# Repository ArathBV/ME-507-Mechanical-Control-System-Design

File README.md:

# ME-507-Mechanical-Control-System-Design
This is a repository containing assignments and coursework from ME 507 Mechanical Control System Design at California Polytechnic State University.

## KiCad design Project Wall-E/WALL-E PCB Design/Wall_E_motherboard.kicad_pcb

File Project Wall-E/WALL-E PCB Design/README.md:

# PCB Design Layout for WALL-E
## Authors: Devon Bolt, Arath Villanueva
- 4 Layer PCB
  - Middle Layer 1, Ground Plane and a 5V bus
  - Middle Layer 2, 3.3V Plane and a 5V bus
    
### Schematic
- 
  - **Full Schematic**

  - **Power Distribution**
### PCB Layout
- 
  - **Top and Bottom Layer**
- 
  - **Middle Layer 1: Ground Plane**
- 
  - **Middle Layer 2: 3.3V Plane**
### PCB CAD Model
-

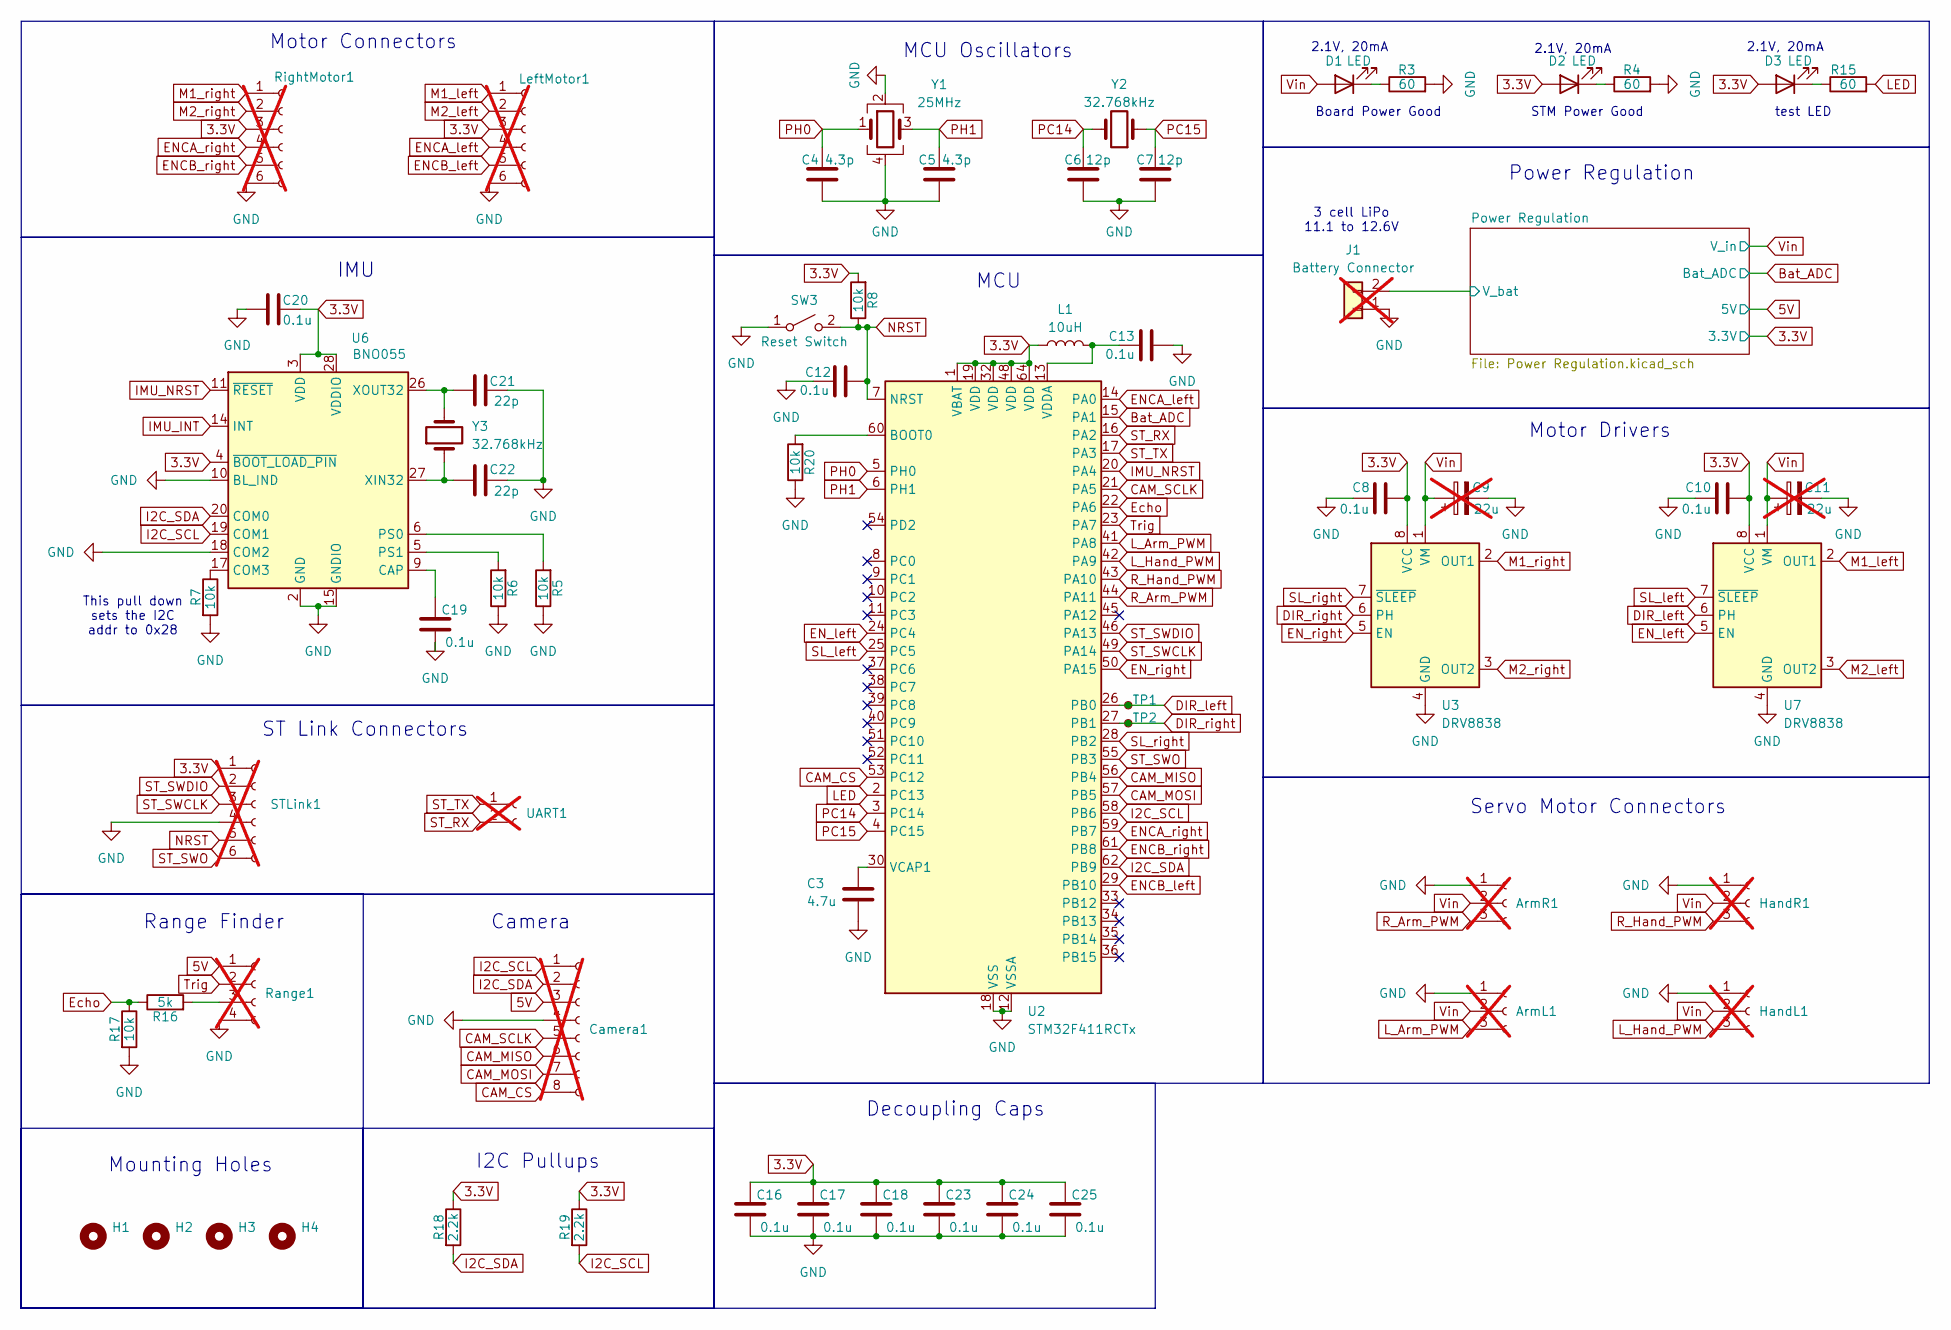
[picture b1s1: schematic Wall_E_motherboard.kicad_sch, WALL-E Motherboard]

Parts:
ArmL1: Conn_01x03_Socket; PinHeader_1x03_P2.54mm_Vertical; not fitted
ArmR1: Conn_01x03_Socket; PinHeader_1x03_P2.54mm_Vertical; not fitted
C3: 4.7u; C_0603_1608Metric
C4, C5: 4.3p; C_0603_1608Metric
C6, C7: 12p; C_0603_1608Metric
C8, C10, C12, C13, C16, C17, C18, C19, C20, C23, C24, C25: 0.1u; C_0603_1608Metric
C9, C11: 22u; CP_Radial_D5.0mm_P2.00mm; not fitted
C21, C22: 22p; C_0603_1608Metric
Camera1: Conn_01x08_Socket; PinHeader_1x08_P2.54mm_Vertical; not fitted
D1, D2, D3: LED; LED_0603_1608Metric
H1, H2, H3, H4: MountingHole; MountingHole_3.2mm_M3
HandL1: Conn_01x03_Socket; PinHeader_1x03_P2.54mm_Vertical; not fitted
HandR1: Conn_01x03_Socket; PinHeader_1x03_P2.54mm_Vertical; not fitted
J1: Conn_01x02; AMASS_XT30PW-M_1x02_P2.50mm_Horizontal; not fitted
L1: 10uH; L_1008_2520Metric
LeftMotor1: Conn_01x06_Socket; PinHeader_1x06_P2.54mm_Vertical; not fitted
R3, R4, R15: 60; R_0603_1608Metric
R5, R6, R7, R8, R17, R20: 10k; R_0603_1608Metric
R16: 5k; R_0603_1608Metric
R18, R19: 2.2k; R_0603_1608Metric
Range1: Conn_01x04_Socket; PinHeader_1x04_P2.54mm_Vertical; not fitted
RightMotor1: Conn_01x06_Socket; PinHeader_1x06_P2.54mm_Vertical; not fitted
STLink1: Conn_01x06_Socket; PinHeader_1x06_P2.54mm_Horizontal; not fitted
SW3: SW_SPST; SW_SPST_PTS645
TP1, TP2: TestPoint_Small; TestPoint_Pad_D1.0mm
U2: STM32F411RCTx; LQFP-64_10x10mm_P0.5mm
U3, U7: DRV8838; WSON-8-1EP_2x2mm_P0.5mm_EP0.9x1.6mm
U6: BNO055; LGA-28_5.2x3.8mm_P0.5mm
UART1: Conn_01x02_Socket; PinHeader_1x02_P2.54mm_Horizontal; not fitted
Y1: 25MHz; Crystal_SMD_3225-4Pin_3.2x2.5mm
Y2, Y3: 32.768kHz; Crystal_SMD_3215-2Pin_3.2x1.5mm

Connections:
3.3V: C8.1, C10.1, C16.1, C17.1, C18.1, C20.2, C23.1, C24.1, C25.1, D2.2 (A), D3.2 (A), L1.1, LeftMotor1.3, R8.2, R18.1, R19.1, RightMotor1.3, STLink1.1, U2.1 (VBAT), U2.19 (VDD), U2.32 (VDD), U2.48 (VDD), U2.64 (VDD), U3.8 (VCC), U6.3 (VDD), U6.4 (~BOOT_LOAD_PIN), U6.28 (VDDIO), U7.8 (VCC); also elsewhere on the board
5V: Camera1.3, Range1.1; also elsewhere on the board
/Power Regulation/V_bat: J1.2; also elsewhere on the board
Bat_ADC: U2.15 (PA1); also elsewhere on the board
CAM_CS: Camera1.8, U2.53 (PC12)
CAM_MISO: Camera1.6, U2.56 (PB4)
CAM_MOSI: Camera1.7, U2.57 (PB5)
CAM_SCLK: Camera1.5, U2.21 (PA5)
DIR_left: TP1.1, U2.26 (PB0), U7.6 (PH)
DIR_right: TP2.1, U2.27 (PB1), U3.6 (PH)
ENCA_left: LeftMotor1.4, U2.14 (PA0)
ENCA_right: RightMotor1.4, U2.59 (PB7)
ENCB_left: LeftMotor1.5, U2.29 (PB10)
ENCB_right: RightMotor1.5, U2.61 (PB8)
EN_left: U2.24 (PC4), U7.5 (EN)
EN_right: U2.50 (PA15), U3.5 (EN)
Echo: R16.1, R17.1, U2.22 (PA6)
GND: ArmL1.1, ArmR1.1, C3.2, C4.2, C5.2, C6.2, C7.2, C8.2, C9.2, C10.2, C11.2, C12.2, C13.2, C16.2, C17.2, C18.2, C19.2, C20.1, C21.2, C22.2, C23.2, C24.2, C25.2, Camera1.4, HandL1.1, HandR1.1, J1.1, LeftMotor1.6, R3.2, R4.2, R5.1, R6.1, R7.2, R17.2, R20.1, Range1.4, RightMotor1.6, STLink1.4, SW3.1 (A), U2.12 (VSSA), U2.18 (VSS), U2.31 (VSS), U2.47 (VSS), U2.63 (VSS), U3.4 (GND), U3.9 (GND), U6.2 (GND), U6.10 (BL_IND), U6.15 (GNDIO), U6.16 (GNDIO), U6.18 (COM2), U6.25 (GNDIO), U7.4 (GND), U7.9 (GND), Y1.2, Y1.4; also elsewhere on the board
I2C_SCL: Camera1.1, R19.2, U2.58 (PB6), U6.19 (COM1)
I2C_SDA: Camera1.2, R18.2, U2.62 (PB9), U6.20 (COM0)
IMU_INT: U6.14 (INT)
IMU_NRST: U2.20 (PA4), U6.11 (~RESET)
LED: R15.2, U2.2 (PC13)
L_Arm_PWM: ArmL1.3, U2.41 (PA8)
L_Hand_PWM: HandL1.3, U2.42 (PA9)
M1_left: LeftMotor1.1, U7.2 (OUT1)
M1_right: RightMotor1.1, U3.2 (OUT1)
M2_left: LeftMotor1.2, U7.3 (OUT2)
M2_right: RightMotor1.2, U3.3 (OUT2)
NRST: C12.1, R8.1, STLink1.5, SW3.2 (B), U2.7 (NRST)
unnamed: D1.1 (K), R3.1
unnamed: D2.1 (K), R4.1
unnamed: D3.1 (K), R15.1
unnamed: R16.2, Range1.3
unnamed: R20.2, U2.60 (BOOT0)
unnamed: C3.1, U2.30 (VCAP1)
unnamed: C13.1, L1.2, U2.13 (VDDA)
unnamed: C19.1, U6.9 (CAP)
unnamed: R7.1, U6.17 (COM3)
unnamed: R5.2, U6.6 (PS0)
unnamed: R6.2, U6.5 (PS1)
unnamed: C22.1, U6.27 (XIN32), Y3.1
unnamed: C21.1, U6.26 (XOUT32), Y3.2
PC14: C6.1, U2.3 (PC14), Y2.2
PC15: C7.1, U2.4 (PC15), Y2.1
PH0: C4.1, U2.5 (PH0), Y1.1
PH1: C5.1, U2.6 (PH1), Y1.3
R_Arm_PWM: ArmR1.3, U2.44 (PA11)
R_Hand_PWM: HandR1.3, U2.43 (PA10)
SL_left: U2.25 (PC5), U7.7 (~SLEEP)
SL_right: U2.28 (PB2), U3.7 (~SLEEP)
ST_RX: U2.16 (PA2), UART1.2
ST_SWCLK: STLink1.3, U2.49 (PA14)
ST_SWDIO: STLink1.2, U2.46 (PA13)
ST_SWO: STLink1.6, U2.55 (PB3)
ST_TX: U2.17 (PA3), UART1.1
Trig: Range1.2, U2.23 (PA7)
Vin: ArmL1.2, ArmR1.2, C9.1, C11.1, D1.2 (A), HandL1.2, HandR1.2, U3.1 (VM), U7.1 (VM); also elsewhere on the board

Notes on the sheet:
Decoupling Caps
STM Power Good
Board Power Good
Range Finder
Power Regulation
Mounting Holes
Camera
MCU Oscillators
Motor Connectors
Servo Motor Connectors
ST Link Connectors
2.1V, 20mA
IMU
Motor Drivers
I2C Pullups
3 cell LiPo 11.1 to 12.6V
test LED
This pull down sets the I2C addr to 0x28
MCU

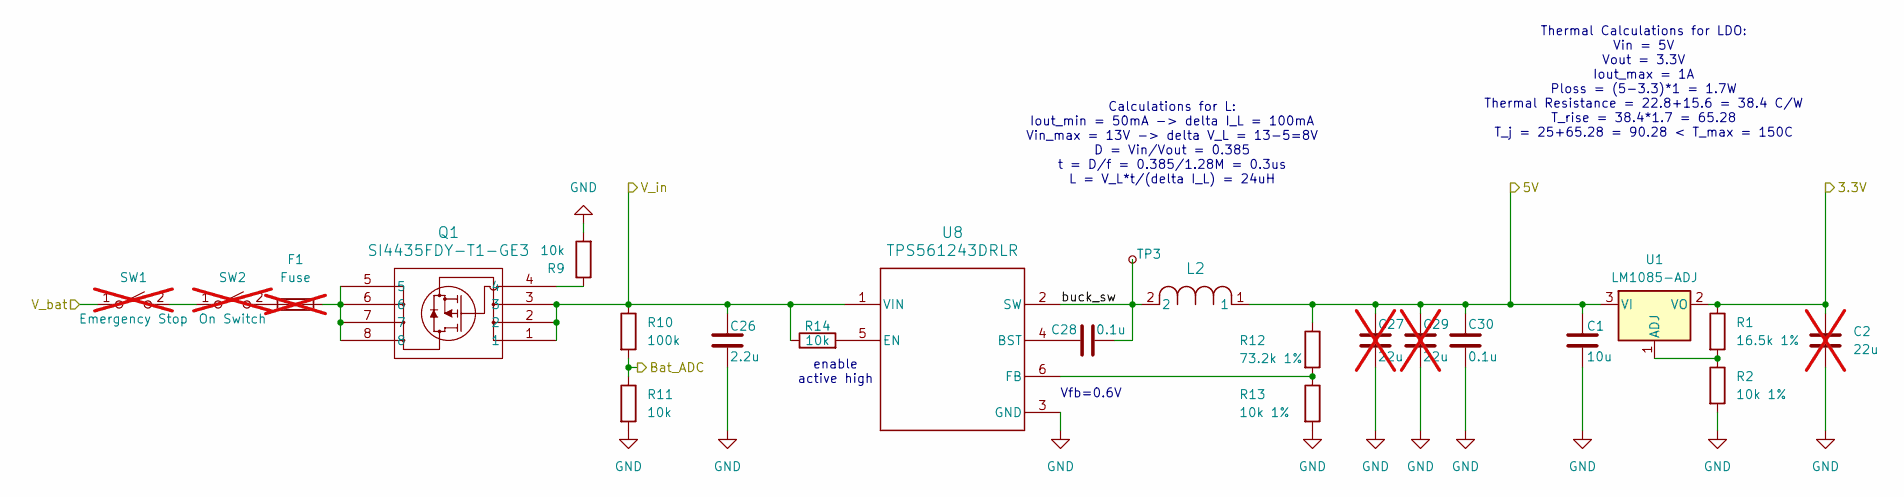
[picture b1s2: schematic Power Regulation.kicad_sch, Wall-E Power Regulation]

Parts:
C1: 10u; C_0603_1608Metric
C2, C27, C29: 22u; CP_Radial_D5.0mm_P2.00mm; not fitted
C26: 2.2u; C_0603_1608Metric
C28, C30: 0.1u; C_0603_1608Metric
F1: Fuse; Fuseholder_Blade_Mini_Keystone_3568; not fitted
L2: IFDC5050HZER270M; IND_IFDC5050HZER_VIS
Q1: SI4435FDY-T1-GE3; SO-8_VIS
R1: 16.5k 1%; R_0603_1608Metric
R2, R13: 10k 1%; R_0603_1608Metric
R9, R11, R14: 10k; R_0603_1608Metric
R10: 100k; R_0603_1608Metric
R12: 73.2k 1%; R_0603_1608Metric
SW1, SW2: SW_SPST; AMASS_XT30PW-F_1x02_P2.50mm_Horizontal; not fitted
TP3: TestPoint_Small; TestPoint_Pad_D1.0mm
U1: LM1085-ADJ; TO-263-3_TabPin2
U8: TPS561243DRLR; DRL0006A-MFG

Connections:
3.3V: C2.1, R1.1, U1.2 (VO); also elsewhere on the board
5V: C1.1, C27.1, C29.1, C30.1, L2.1, R12.1, U1.3 (VI); also elsewhere on the board
/Power Regulation/V_bat: SW1.1 (A); also elsewhere on the board
/Power Regulation/buck_sw: C28.2, L2.2, TP3.1, U8.2 (SW)
Bat_ADC: R10.2, R11.1; also elsewhere on the board
GND: C1.2, C2.2, C26.2, C27.2, C29.2, C30.2, R2.2, R9.2, R11.2, R13.2, U8.3 (GND); also elsewhere on the board
unnamed: F1.2, Q1.5, Q1.6, Q1.7, Q1.8
unnamed: Q1.4, R9.1
unnamed: SW1.2 (B), SW2.1 (A)
unnamed: F1.1, SW2.2 (B)
unnamed: R1.2, R2.1, U1.1 (ADJ)
unnamed: C28.1, U8.4 (BST)
unnamed: R14.2, U8.5 (EN)
unnamed: R12.2, R13.1, U8.6 (FB)
Vin: C26.1, Q1.1, Q1.2, Q1.3, R10.1, R14.1, U8.1 (VIN); also elsewhere on the board

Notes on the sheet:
Vfb=0.6V
Calculations for L: Iout_min = 50mA -> delta I_L = 100mA Vin_max = 13V -> delta V_L = 13-5=8V D = Vin/Vout = 0.385 t = D/f = 0.385/1.28M = 0.3us L = V_L*t/(delta I_L) = 24uH
enable active high
Thermal Calculations for LDO: Vin = 5V Vout = 3.3V Iout_max = 1A Ploss = (5-3.3)*1 = 1.7W Thermal Resistance = 22.8+15.6 = 38.4 C/W T_rise = 38.4*1.7 = 65.28 T_j = 25+65.28 = 90.28 < T_max = 150C

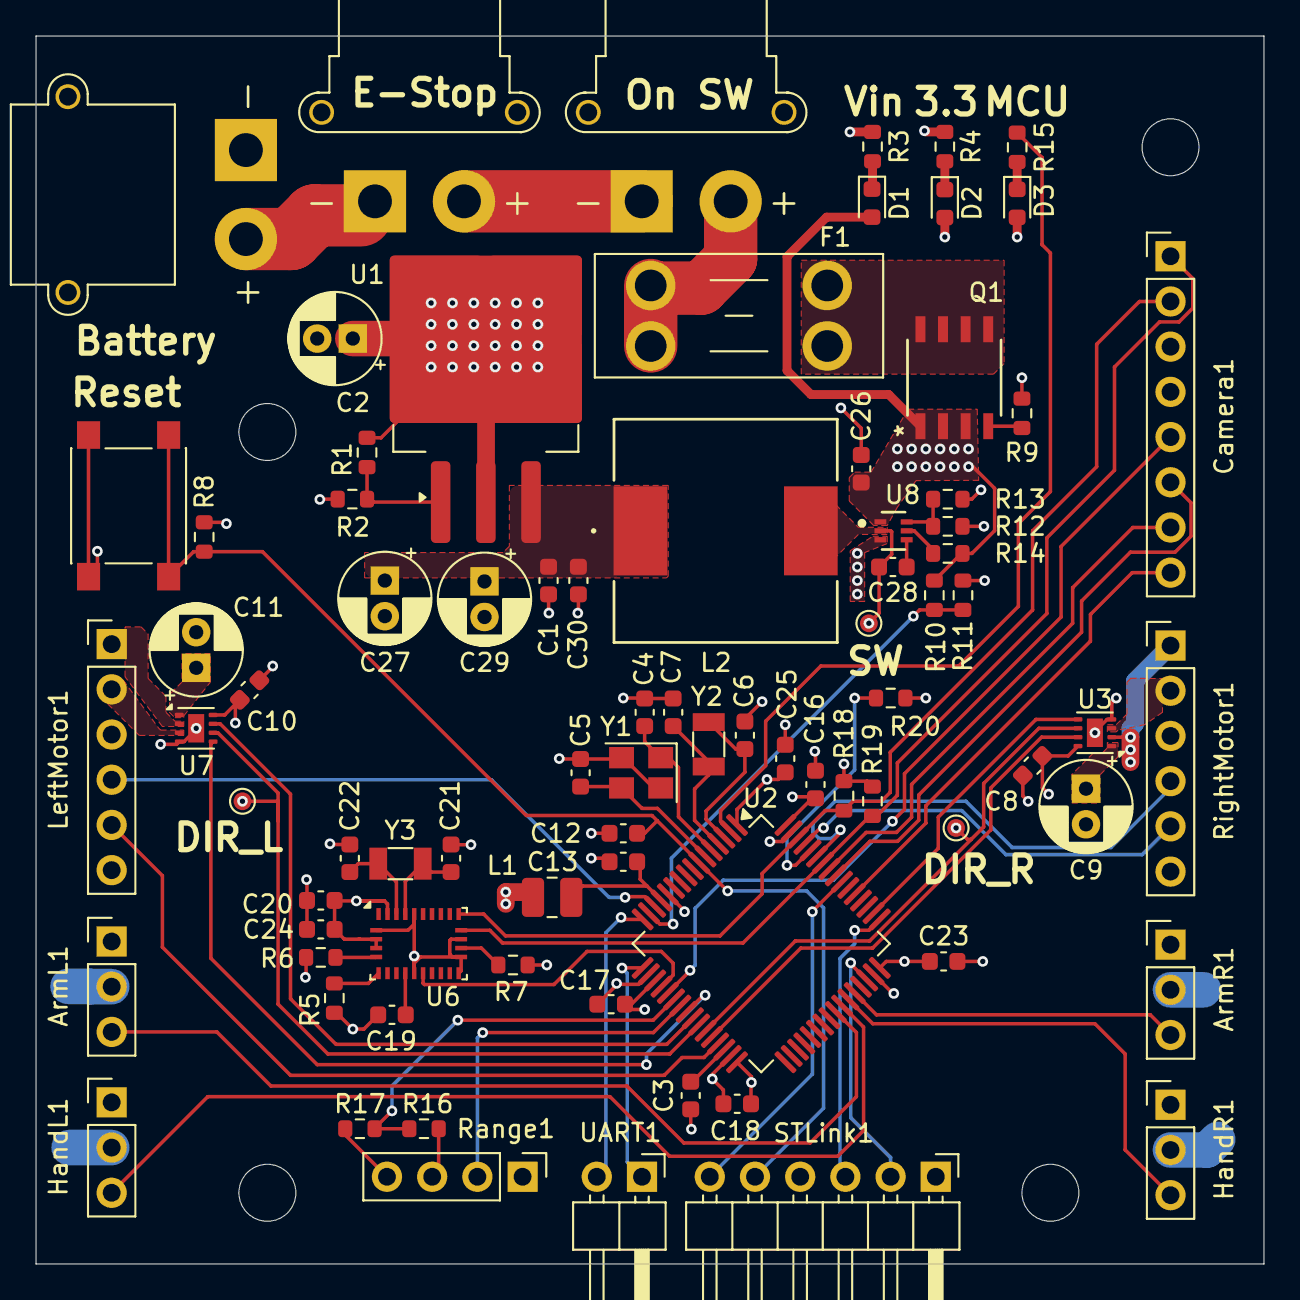
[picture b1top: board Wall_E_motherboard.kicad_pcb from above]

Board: 4 copper layers, 69.0 x 69.0 mm, 85 parts (0 on the bottom side), 66 nets.

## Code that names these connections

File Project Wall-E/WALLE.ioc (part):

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Mcu.Name=STM32F411R(C-E)Tx
Mcu.Package=LQFP64
Mcu.UserName=STM32F411RETx
PA0-WKUP.GPIOParameters=GPIO_Label
PA0-WKUP.GPIO_Label=ENCA_Left
PA0-WKUP.Signal=S_TIM2_CH1_ETR
PA1.GPIOParameters=GPIO_Label
PA1.GPIO_Label=Bat_ADC
PA1.Signal=ADCx_IN1
PA10.GPIOParameters=GPIO_Label
PA10.GPIO_Label=R_HandPWM
PA10.Signal=S_TIM1_CH3
PA11.GPIOParameters=GPIO_Label
PA11.GPIO_Label=R_Arm_PWM
PA11.Signal=S_TIM1_CH4
PA13.Mode=Trace_Asynchronous_SW
PA13.Signal=SYS_JTMS-SWDIO
PA14.Mode=Trace_Asynchronous_SW
PA14.Signal=SYS_JTCK-SWCLK
PA15.GPIOParameters=GPIO_Label
PA15.GPIO_Label=EN_Right
PA15.Signal=GPIO_Output
PA2.Mode=Asynchronous
PA2.Signal=USART2_TX
PA3.Mode=Asynchronous
PA3.Signal=USART2_RX
PA4.GPIOParameters=GPIO_Label
PA4.GPIO_Label=IMU_NRST
PA4.Signal=GPIO_Output
PA5.GPIOParameters=GPIO_Label
PA5.GPIO_Label=CAM_SCLK
PA5.Mode=Full_Duplex_Master
PA5.Signal=SPI1_SCK
PA6.GPIOParameters=GPIO_Label
PA6.GPIO_Label=Trig
PA6.Signal=S_TIM3_CH1
PA7.GPIOParameters=GPIO_Label
PA7.GPIO_Label=CAM_MOSI
PA7.Mode=Full_Duplex_Master
PA7.Signal=SPI1_MOSI
PA8.GPIOParameters=GPIO_Label
PA8.GPIO_Label=L_ArmPWM
PA8.Signal=S_TIM1_CH1
PA9.GPIOParameters=GPIO_Label
PA9.GPIO_Label=L_HandPWM
PA9.Signal=S_TIM1_CH2
PB0.GPIOParameters=GPIO_Label
PB0.GPIO_Label=DIR_Left
PB0.Signal=S_TIM3_CH3
PB1.GPIOParameters=GPIO_Label
PB1.GPIO_Label=DIR_Right
PB1.Signal=S_TIM3_CH4
PB10.GPIOParameters=GPIO_Label
PB10.GPIO_Label=ENCB_Left
PB10.Signal=S_TIM2_CH3
PB2.Signal=GPIO_Output
PB3.Mode=Trace_Asynchronous_SW
PB3.Signal=SYS_JTDO-SWO
PB4.GPIOParameters=GPIO_Label
PB4.GPIO_Label=CAM_MISO
PB4.Mode=Full_Duplex_Master
PB4.Signal=SPI1_MISO
PB5.GPIOParameters=GPIO_Label
PB5.GPIO_Label=Echo
PB5.Signal=S_TIM3_CH2
PB6.Mode=I2C
PB6.Signal=I2C1_SCL
PB7.GPIOParameters=GPIO_Label
PB7.GPIO_Label=ENCA_Right
PB7.Signal=S_TIM4_CH2
PB8.GPIOParameters=GPIO_Label
PB8.GPIO_Label=ENCB_Right
PB8.Signal=S_TIM4_CH3
PB9.Mode=I2C
PB9.Signal=I2C1_SDA
PC12.GPIOParameters=GPIO_Label
PC12.GPIO_Label=CAM_CS
PC12.Signal=GPIO_Output
PC13-ANTI_TAMP.Signal=GPIO_Output
PC4.GPIOParameters=GPIO_Label
PC4.GPIO_Label=EN_Left
PC4.Signal=GPIO_Output
PC5.GPIOParameters=GPIO_Label
PC5.GPIO_Label=SL_Left
PC5.Signal=GPIO_Output
PH0\ -\ OSC_IN.Mode=HSE-External-Oscillator
PH0\ -\ OSC_IN.Signal=RCC_OSC_IN
PH1\ -\ OSC_OUT.Mode=HSE-External-Oscillator
PH1\ -\ OSC_OUT.Signal=RCC_OSC_OUT
RCC.HSE_VALUE=25000000
RCC.SYSCLKFreq_VALUE=16000000
board=custom

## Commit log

2025-04-04 Blinky main program
2025-04-05 Blinky Overview and Takeaways
2025-04-05 Lab Assignments Lists
2025-04-05 Demo Added.
2025-04-05 8 Bit Switch Dip Design Files
2025-04-06 Homework 0 Pictures Added
2025-04-11 Blinky Led with Timers Program
2025-04-18 Motor Driver now updating PWM Signal
2025-04-18 Motor Driver Header
2025-04-18 Motor Driver
2025-04-21 Homework 2
2025-05-01 WALLE ioc, Pin and Peripherals Setups V1
2025-05-01 WALLE Testing ioc
2025-05-01 Ultrasonic Sensor and Bluetooth header files
2025-05-01 Updated Wall-E test ioc
2025-05-01 Updated Wall-E ioc
2025-05-08 Updated Comments on Files
2025-05-08 Updated ioc for WALLE
2025-05-08 New WALLE ioc with correct MCU
2025-05-08 WALLE Board IMU Header File
2025-05-08 Class implementation HCSR04.h
2025-05-08 IMU: MPU6050 Starter Header File
2025-05-18 KiCAD PCB Files
2025-05-20 Homework 3 starter files
2025-05-20 New Classes
2025-05-26 Homework 5 Complete
2025-06-09 IMU and Ultrasonic Sensor Header and Class files
2025-06-10 Sensor Drivers Ready for Testing
2025-06-10 Updated IOC
2025-06-10 ADC implemented for Battery Status
2025-06-10 Updated and Tested Files
2025-06-10 Updated and Corrected ioc
2025-06-11 Romi Motor Changes and Interupt with TIM5 PWM
2025-06-11 Sensor Checks in Beginning
2025-06-11 Interrupt Enabled
2025-06-11 Adding start to stop angle Func. Servo Class Good
2025-06-11 Servo Motors Added to main
2025-06-11 PID Controller Added for sensor fusion/movement
2025-06-11 Most Updated Files
2025-06-11 Updated Files with WALLE FSM
2025-06-11 Added a simple FSM without PID control
2025-06-11 Added Simple Control Testing
